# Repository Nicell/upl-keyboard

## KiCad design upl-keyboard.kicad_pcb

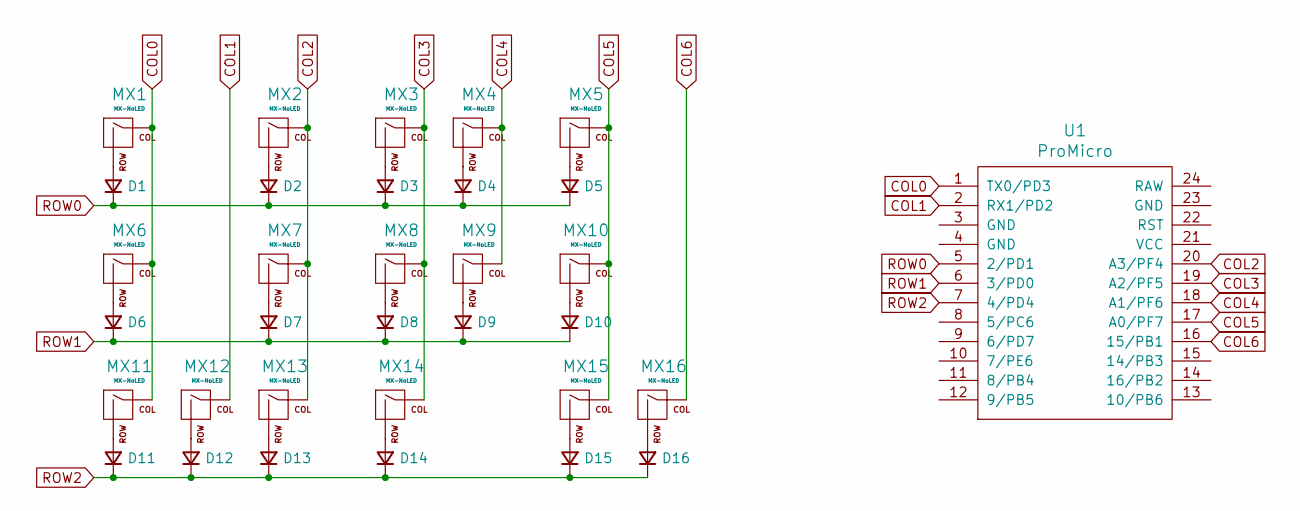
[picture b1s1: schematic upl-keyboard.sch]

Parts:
D1, D2, D3, D4, D5, D6, D7, D8, D9, D10, D11, D12, D13, D14, D15, D16: D_Small; D_SOD-123F
MX1, MX2, MX3, MX4, MX5, MX6, MX7, MX8, MX9, MX10, MX11, MX12, MX13, MX14, MX15, MX16: MX-NoLED; MXOnly-1U-NoLED
U1: ProMicro; ArduinoProMicro

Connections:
COL0: MX1.1 (COL), MX6.1 (COL), MX11.1 (COL), U1.1 (TX0/PD3)
COL1: MX12.1 (COL), U1.2 (RX1/PD2)
COL2: MX2.1 (COL), MX7.1 (COL), MX13.1 (COL), U1.20 (A3/PF4)
COL3: MX3.1 (COL), MX8.1 (COL), MX14.1 (COL), U1.19 (A2/PF5)
COL4: MX4.1 (COL), MX9.1 (COL), U1.18 (A1/PF6)
COL5: MX5.1 (COL), MX10.1 (COL), MX15.1 (COL), U1.17 (A0/PF7)
COL6: MX16.1 (COL), U1.16 (15/PB1)
unnamed: D1.2 (A), MX1.2 (ROW)
unnamed: D2.2 (A), MX2.2 (ROW)
unnamed: D3.2 (A), MX3.2 (ROW)
unnamed: D4.2 (A), MX4.2 (ROW)
unnamed: D5.2 (A), MX5.2 (ROW)
unnamed: D6.2 (A), MX6.2 (ROW)
unnamed: D7.2 (A), MX7.2 (ROW)
unnamed: D8.2 (A), MX8.2 (ROW)
unnamed: D9.2 (A), MX9.2 (ROW)
unnamed: D10.2 (A), MX10.2 (ROW)
unnamed: D11.2 (A), MX11.2 (ROW)
unnamed: D12.2 (A), MX12.2 (ROW)
unnamed: D13.2 (A), MX13.2 (ROW)
unnamed: D14.2 (A), MX14.2 (ROW)
unnamed: D15.2 (A), MX15.2 (ROW)
unnamed: D16.2 (A), MX16.2 (ROW)
ROW0: D1.1 (K), D2.1 (K), D3.1 (K), D4.1 (K), D5.1 (K), U1.5 (2/PD1)
ROW1: D6.1 (K), D7.1 (K), D8.1 (K), D9.1 (K), D10.1 (K), U1.6 (3/PD0)
ROW2: D11.1 (K), D12.1 (K), D13.1 (K), D14.1 (K), D15.1 (K), D16.1 (K), U1.7 (4/PD4)

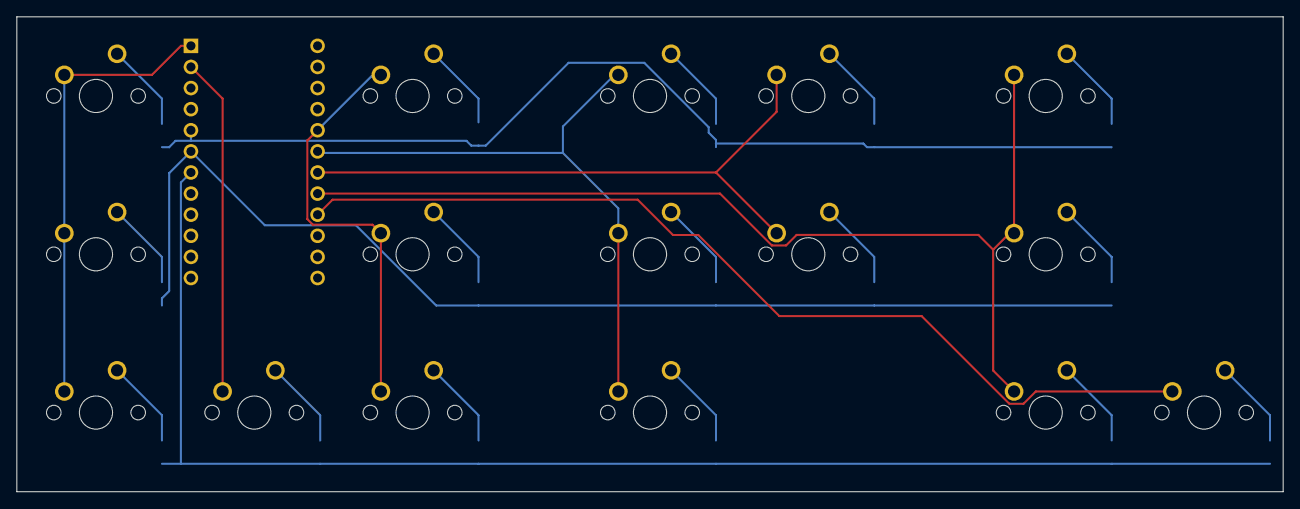
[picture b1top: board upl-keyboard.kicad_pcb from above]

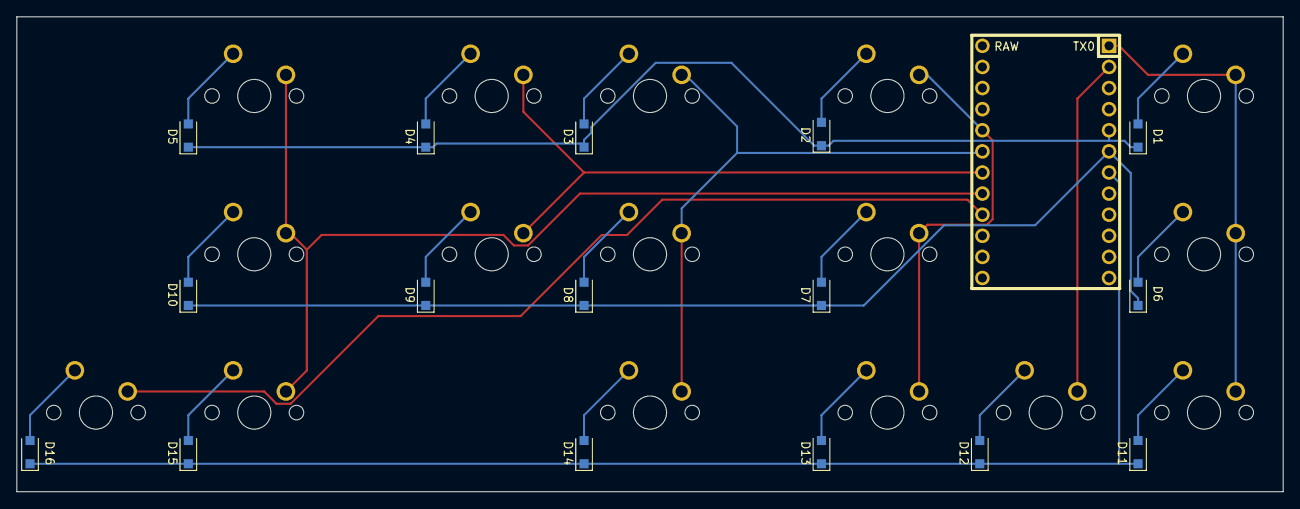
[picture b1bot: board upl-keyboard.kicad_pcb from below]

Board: 2 copper layers, 152.4 x 57.2 mm, 33 parts (16 on the bottom side), 26 nets.

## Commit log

2021-10-18 init commit
2021-10-18 update schematic
